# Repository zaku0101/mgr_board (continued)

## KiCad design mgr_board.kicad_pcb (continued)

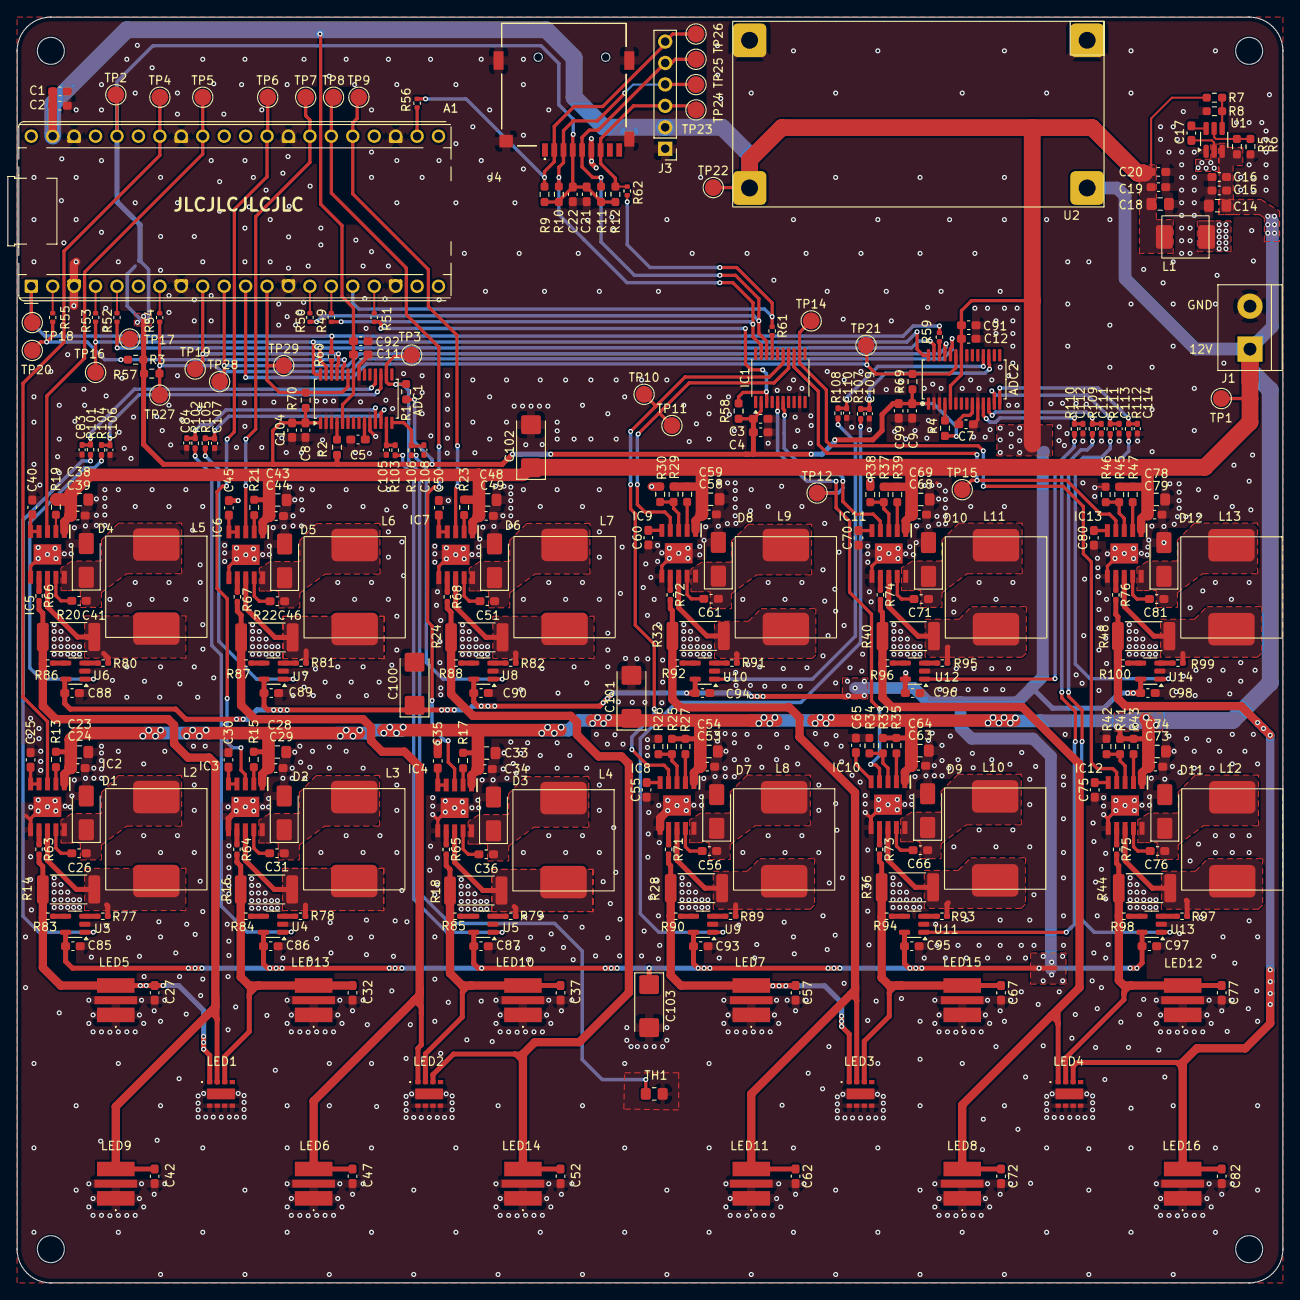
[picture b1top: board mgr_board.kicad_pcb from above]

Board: 2 copper layers, 150.0 x 150.0 mm, 331 parts (1 on the bottom side), 189 nets.

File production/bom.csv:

Designator,Footprint,Quantity,Value,LCSC Part #
A1,RaspberryPi_Pico_Common_THT,1,Pi_Pico,
"ADC1, ADC2",TSSOP-28_4.4x9.7mm_P0.65mm,2,ADS1148QPWRQ1,
"C1, C104, C21, C24, C29, C3, C34, C39, C44, C49, C54, C59, C64, C69, C74, C79, C91, C92, C99",0603,19,"4,7uF",C19666
"C100, C101, C102, C103",CP_EIA-6032-15_Kemet-U_Pad2.25x2.35mm_HandSolder,4,47uF,
"C105, C106, C107, C108, C109, C110, C111, C112, C113, C114, C83, C84",0402,12,1nF,C1523
"C11, C12, C16, C17, C2, C20, C22, C26, C27, C31, C32, C36, C37, C4, C41, C42, C46, C47, C51, C52, C56, C57, C61, C62, C66, C67, C71, C72, C76, C77, C8, C81, C82, C85, C86, C87, C88, C89, C9, C90, C93, C94, C95, C96, C97, C98",0603,46,100nF,C14663
"C14, C18, C23, C28, C33, C38, C43, C48, C53, C58, C63, C68, C73, C78",0805,14,22uF,C96446
"C15, C19",0603,2,10uF,C45783
"C25, C30, C35, C40, C45, C5, C50, C55, C60, C65, C7, C70, C75, C80",0603,14,1uF,C15849
"D1, D10, D11, D12, D2, D3, D4, D5, D6, D7, D8, D9",D_SMA,12,SS34,C8678
IC1,TSSOP-20_4.4x6.5mm_P0.65mm,1,MCP48CVB08-20E_ST,
"IC10, IC11, IC12, IC13, IC2, IC3, IC4, IC5, IC6, IC7, IC8, IC9",SOP100P600X165-11N,12,A6214KLKTR-T,C146400
J1,TerminalBlock_bornier-2_P5.08mm,1,Screw_Terminal_2_P5.00mm,
J3,PinHeader_1x06_P2.54mm_Vertical,1,SD Card SPI Module,
J4,MCSPQ08ASGTR,1,Micro_SD_Card,
L1,HPIO530-4R7,1,"4,7uH",C408410
"L10, L11, L12, L13, L2, L3, L4, L5, L6, L7, L8, L9",DR125-470-R,12,47 uH 2A,C5127262
"LED1, LED2, LED3, LED4",XPLDCL,4,XPLDCL-00-0000-0000HC6AAAE7,
"LED10, LED11, LED12, LED13, LED14, LED15, LED16, LED5, LED6, LED7, LED8, LED9",JR5050CWT,12,JR5050CWT-E-B50EB0000-N0000001,
R1,0603,1,1k,C21190
"R10, R11, R12, R2, R25, R29, R3, R33, R37, R4, R41, R45, R5, R57, R58, R6, R69, R70, R8, R9",0603,20,10k,C25804
"R100, R63, R64, R65, R66, R67, R68, R71, R72, R73, R74, R75, R76, R77, R78, R79, R80, R81, R82, R83, R84, R85, R86, R87, R88, R89, R90, R91, R92, R93, R94, R95, R96, R97, R98, R99",0402,36,0R,C17168
"R101, R102, R103, R104, R105, R106, R107, R108, R109, R110, R111, R112",0402,12,"1,5k", C25867
"R13, R15, R17, R19, R21, R23, R27, R31, R35, R39, R43, R47",0603,12,442k,C23175
"R14, R16, R18, R20, R22, R24",2512,6,R150 or R250,
"R26, R30, R34, R38, R42, R46",0603,6,2k,C22975
"R28, R32, R36, R40, R44, R48",2512,6,R180 or R250,
R7,0603,1,56k,C23206
TH1,0805,1,NTC 2.2k,
"TP1, TP10, TP11, TP12, TP13, TP14, TP15, TP16, TP17, TP18, TP19, TP2, TP20, TP21, TP22, TP23, TP24, TP25, TP26, TP27, TP28, TP29, TP3, TP4, TP5, TP6, TP7, TP8, TP9",TestPoint_Pad_D2.0mm,29,TestPoint,
U1,SOT-23-6_Handsoldering,1,TPS562201DDCR,C90061
"U10, U11, U12, U13, U14, U9",SOT-23-5,6,INA180A1,
U2,LM2596 DC-DC module,1,LM2596 BUCK MODULE,
"U3, U4, U5, U6, U7, U8",SOT-23-5,6,INA180A1,C122228

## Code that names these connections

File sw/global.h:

//data
#define NUM_SPI_ADC_CHANNELS 14
#define MEAS_DATA_BUFF_SIZE 28
#define FILENAME "data.csv"
#define DAC_CHANNELS 6
//uart
#define UART_ID uart0
#define BAUD_RATE 115200
#define UART_TX_PIN 0  
#define UART_RX_PIN 1  

//spi0 pins
#define SPI0_MISO 0
#define SPI0_MOSI 3
#define SPI0_SCK 2

//spi1 pins
#define SPI1_MISO 12
#define SPI1_MOSI 11
#define SPI1_SCK 10

#define ADC0_CS 1
#define ADC1_CS 5
#define DAC_CS 13 
#define SD_CS 17

//adc control pins
#define ADC0_DRDY 6
#define ADC1_DRDY 7
#define ADC1_START 8
#define ADC0_START 9

#define NUMBER_OF_ADC_CHANNELS 7

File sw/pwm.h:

#include "pico/stdlib.h"
#include "hardware/pwm.h"

#define PWM_0 28
#define PWM_1 27
#define PWM_2 22
#define PWM_3 21
#define PWM_4 20
#define PWM_5 19

//standard PWM levels
#define PWM_LEVEL_0 50000
#define PWM_LEVEL_1 62500

//reduced PWM levels for debugging
// #define PWM_LEVEL_0 300
// #define PWM_LEVEL_1 300

#define PWM_SYSCLK_DIV 2

#define PWM_DUTY ((uint16_t) 62500)


void init_pwm();
void setup_pwm_settings();

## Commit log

2024-12-06 draft
2025-02-20 First board schematic version
2025-02-23 reviewed
2025-02-23 fixing review suggestions
2025-02-23 small changes
2025-02-25 elo2
2025-02-27 first complete version schematics
2025-03-05 Changed footprints of passive elements, reviewed
2025-03-06 changing footprint for buck converter coil
2025-03-09 Commit after kicad fuckup project
2025-03-09 drc fixes
2025-03-09 eloleo
2025-03-09 final
2025-03-10 finished boarD
2025-03-12 adding sw part
2025-03-17 Fixed bugs after reviews
2025-03-18 Added pdfs
2025-03-20 Added current sense amplifier, reduced one ADC, changed elec cap to tantals, to review
2025-03-20 Added low pass filters at current sense amp outputs and pull ups on cs pins, DRC done
2025-03-20 updated production files
2025-03-21 fixed some kutases
2025-03-24 sw init
2025-03-24 removing unecessary files from tracking
2025-03-25 adding DAC driver
2025-03-26 adding ADC driver code defining register and command values for communication, and adding draft of communication functions
2025-03-28 adding functions initalizing and sending commands to adc
2025-03-29 finishing adc handling and adding pwm for diodes
2025-03-31 adding saving data from buffers to sd card csv file and adding interrupt drived ADC measurements as in datasheet
2025-03-31 trying to fix interrupt settings to work
2025-04-03 fixing bugs not really
2025-04-05 fixing dac and adc communication
2025-04-14 setting pwm and dac values
2025-04-14 fixing bugs
2025-05-17 adding mux
2025-05-19 eluwina
2025-05-19 eloo
2025-05-19 eluwski
2025-05-19 elooowski
2025-05-20 elooo
2025-05-20 Update ADS1148.c
    chuj w dupe policji
2025-05-20 finish this shit
2025-05-29 finishing working code
2025-05-29 konieec
2025-06-04 grande finite
